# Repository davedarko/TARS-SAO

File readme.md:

# TARS inspired Simple Add-on
A small but powerful display, 6 touch buttons, a speaker and an LED.

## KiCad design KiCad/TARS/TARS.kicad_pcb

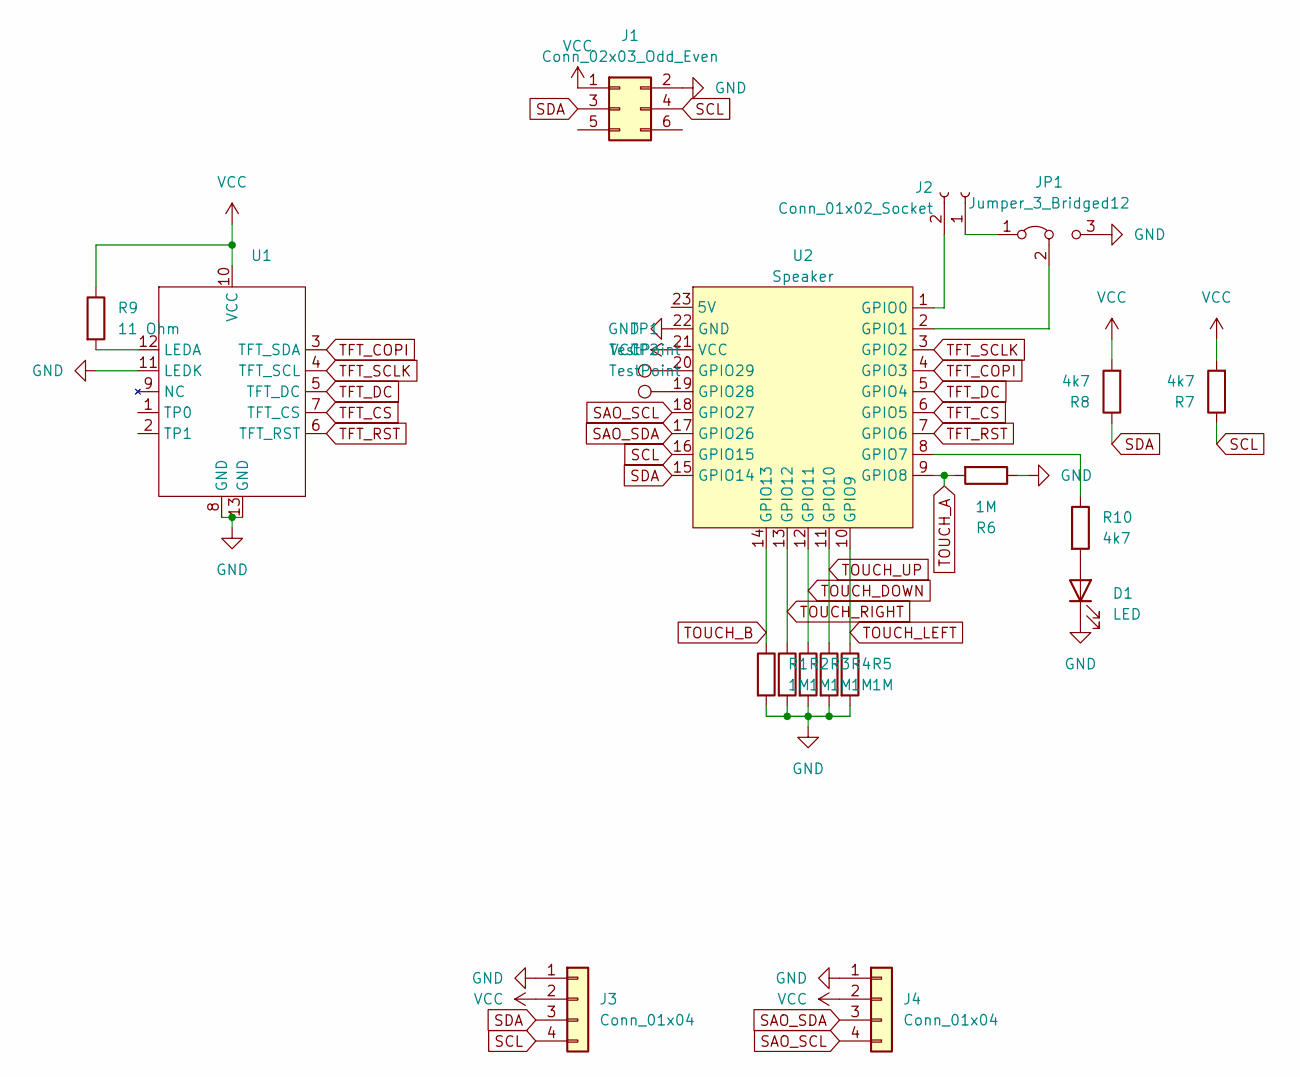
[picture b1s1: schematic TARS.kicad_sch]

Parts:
D1: LED; D_0603_1608Metric_Pad1.05x0.95mm_HandSolder
J1: Conn_02x03_Odd_Even; IDC-Header_2x03_P2.54mm_Vertical_SMD
J2: Conn_01x02_Socket; Molex_PicoBlade_53261-0271_1x02-1MP_P1.25mm_Horizontal
J3, J4: Conn_01x04; JST_SH_SM04B-SRSS-TB_1x04-1MP_P1.00mm_Horizontal
JP1: Jumper_3_Bridged12; SolderJumper-3_P1.3mm_Bridged12_RoundedPad1.0x1.5mm
R1, R2, R3, R4, R5, R6: 1M; R_0603_1608Metric_Pad0.98x0.95mm_HandSolder
R7, R8, R10: 4k7; R_0603_1608Metric_Pad0.98x0.95mm_HandSolder
R9: 11 Ohm; R_0603_1608Metric_Pad0.98x0.95mm_HandSolder
TP1, TP2: TestPoint; TestPoint_Pad_D1.5mm
U1: ST7735S-160x80-13PIN
U2: Speaker; RP2040-TINY; MPN C132528

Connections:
GND: D1.1 (K), J1.2, J3.1, J4.1, JP1.3 (B), R1.2, R2.2, R3.2, R4.2, R5.2, R6.1, U1.8 (GND), U1.11 (LEDK), U1.13 (GND), U2.22 (GND)
unnamed: D1.2 (A), R10.2
unnamed: J2.1, JP1.1 (A)
unnamed: J2.2, U2.1 (GPIO0)
unnamed: JP1.2 (C), U2.2 (GPIO1)
unnamed: R9.2, U1.12 (LEDA)
unnamed: R10.1, U2.8 (GPIO7)
unnamed: TP2.1, U2.19 (GPIO28)
unnamed: TP1.1, U2.20 (GPIO29)
SAO_SCL: J4.4, U2.18 (GPIO27)
SAO_SDA: J4.3, U2.17 (GPIO26)
SCL: J1.4, J3.4, R7.1, U2.16 (GPIO15)
SDA: J1.3, J3.3, R8.1, U2.15 (GPIO14)
TFT_COPI: U1.3 (TFT_SDA), U2.4 (GPIO3)
TFT_CS: U1.7 (TFT_CS), U2.6 (GPIO5)
TFT_DC: U1.5 (TFT_DC), U2.5 (GPIO4)
TFT_RST: U1.6 (TFT_RST), U2.7 (GPIO6)
TFT_SCLK: U1.4 (TFT_SCL), U2.3 (GPIO2)
TOUCH_A: R6.2, U2.9 (GPIO8)
TOUCH_B: R1.1, U2.14 (GPIO13)
TOUCH_DOWN: R3.1, U2.12 (GPIO11)
TOUCH_LEFT: R5.1, U2.10 (GPIO9)
TOUCH_RIGHT: R2.1, U2.13 (GPIO12)
TOUCH_UP: R4.1, U2.11 (GPIO10)
VCC: J1.1, J3.2, J4.2, R7.2, R8.2, R9.1, U1.10 (VCC), U2.21 (VCC)

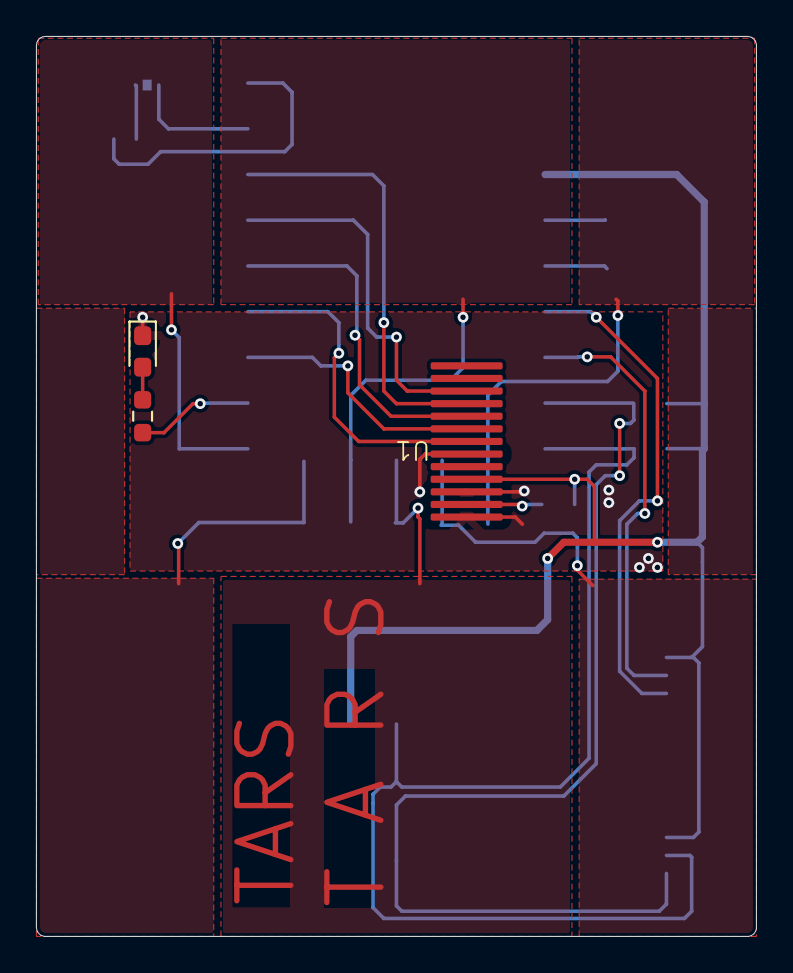
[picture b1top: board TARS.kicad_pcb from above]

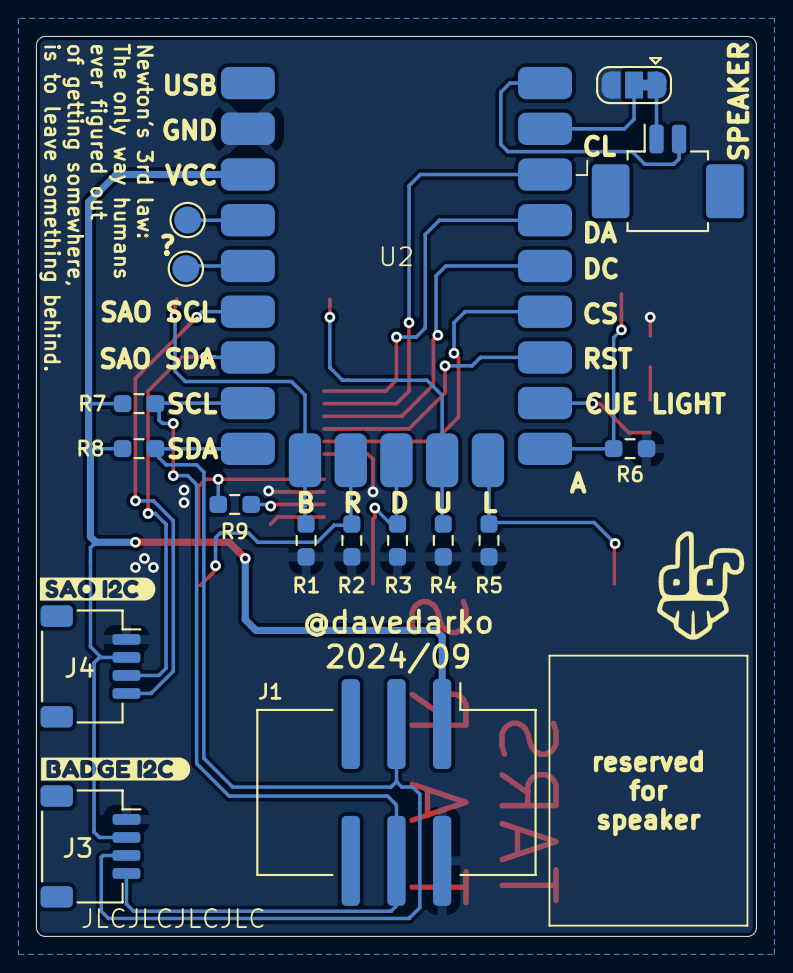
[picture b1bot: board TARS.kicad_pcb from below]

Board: 2 copper layers, 40.0 x 50.0 mm, 23 parts (20 on the bottom side), 25 nets.

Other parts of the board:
Ref**: Val**; davedarko_logo_silk_outline
kibuzzard-66F128E4: G***; kibuzzard-66F128E4
kibuzzard-66F12846: G***; kibuzzard-66F12846

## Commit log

2024-10-05 first succesful order
2024-10-10 menu added
